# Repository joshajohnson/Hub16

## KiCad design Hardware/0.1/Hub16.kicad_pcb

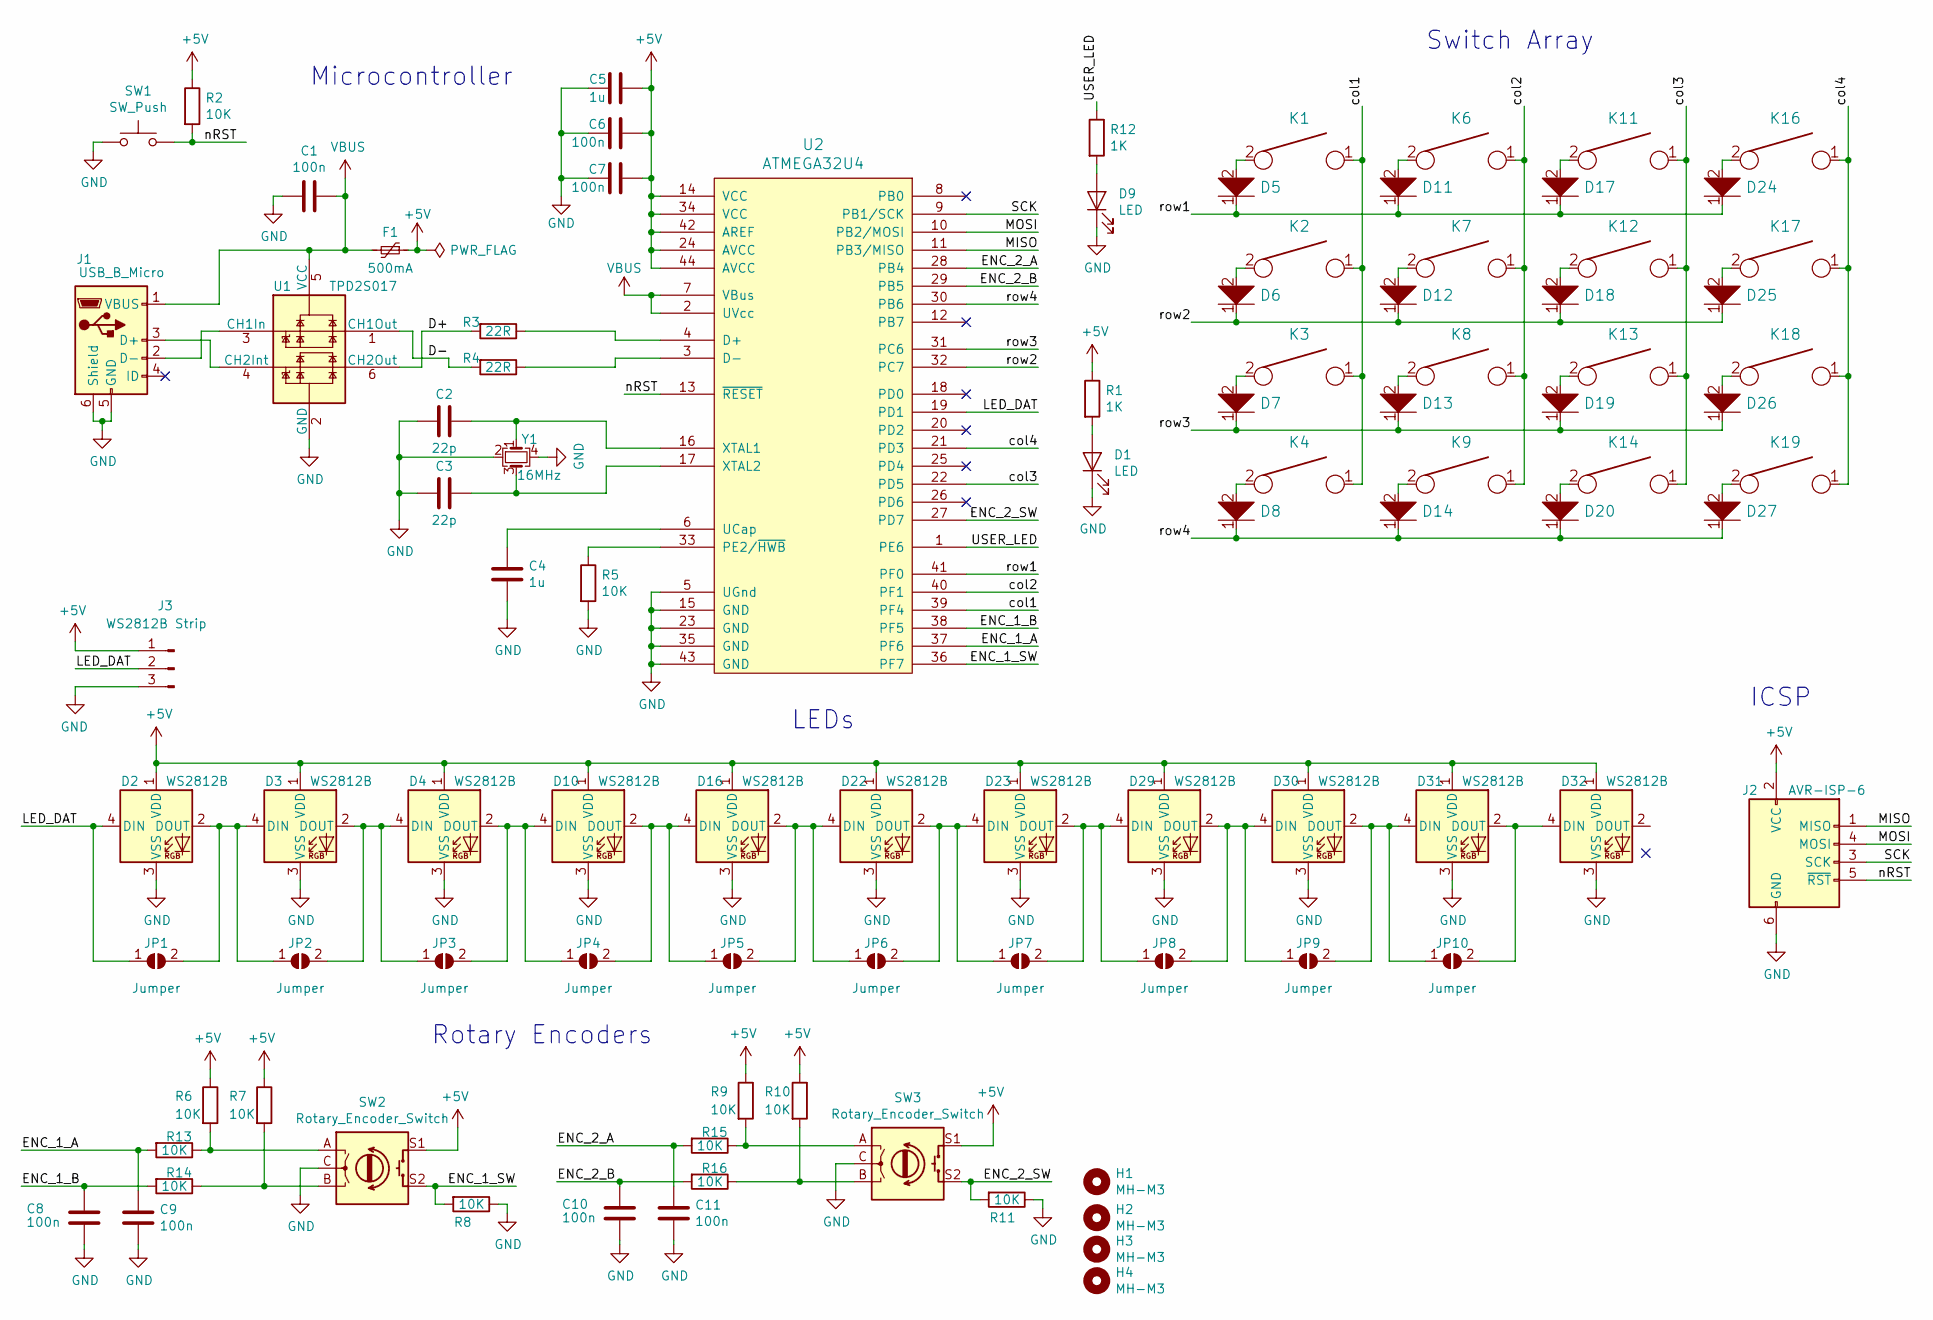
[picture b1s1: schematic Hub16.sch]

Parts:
C1, C6, C7, C8, C9, C10, C11: 100n; C_0603_1608Metric
C2, C3: 22p; C_0603_1608Metric
C4, C5: 1u; C_0603_1608Metric
D1, D9: LED; LED_0603_1608Metric
D2, D3, D4, D10, D16, D22, D23, D29, D30, D31, D32: WS2812B; LED_WS2812B_PLCC4_5.0x5.0mm_P3.2mm
D5, D6, D7, D8, D11, D12, D13, D14, D17, D18, D19, D20, D24, D25, D26, D27: D; D_SOD-323
F1: 500mA; Fuse_0805_2012Metric
H1, H2, H3, H4: MH-M3; MountingHole_3.2mm_M3_ISO14580
J1: USB_B_Micro; MicroUSB_Aliexpress
J2: AVR-ISP-6; AVR_Programmer_SMD
J3: WS2812B Strip; PinPad_1x03_P2.54mm
JP1, JP2, JP3, JP4, JP5, JP6, JP7, JP8, JP9, JP10: Jumper; SolderJumper-2_P1.3mm_Open_RoundedPad1.0x1.5mm
K1, K2, K3, K4, K6, K7, K8, K9, K11, K12, K13, K14, K16, K17, K18, K19: KEYSW; SW_Cherry_MX1A_1.00u_PCB
R1, R12: 1K; R_0603_1608Metric
R2, R5, R6, R7, R8, R9, R10, R11, R13, R14, R15, R16: 10K; R_0603_1608Metric
R3, R4: 22R; R_0603_1608Metric
SW1: SW_Push; Small_Tact_Switch
SW2, SW3: Rotary_Encoder_Switch; RotaryEncoder_Alps_EC11E-Switch_Vertical_H20mm_CircularMoun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
U1: TPD2S017; SOT-23-6
U2: ATMEGA32U4; TQFP-44_10x10mm_P0.8mm
Y1: 16MHz; Crystal_SMD_3225-4Pin_3.2x2.5mm

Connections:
+5V: C5.1, C6.2, C7.2, D2.1 (VDD), D3.1 (VDD), D4.1 (VDD), D10.1 (VDD), D16.1 (VDD), D22.1 (VDD), D23.1 (VDD), D29.1 (VDD), D30.1 (VDD), D31.1 (VDD), D32.1 (VDD), F1.1, J2.2 (VCC), J3.1, R1.1, R2.1, R6.1, R7.1, R9.1, R10.1, SW2.S1, SW3.S1, U2.14 (VCC), U2.24 (AVCC), U2.34 (VCC), U2.42 (AREF), U2.44 (AVCC)
/D+: R3.2, U1.6 (CH2Out)
/D-: R4.2, U1.1 (CH1Out)
/ENC_1_A: C9.1, R13.2, U2.37 (PF6)
/ENC_1_B: C8.1, R14.2, U2.38 (PF5)
/ENC_1_SW: R8.2, SW2.S2, U2.36 (PF7)
/ENC_2_A: C11.1, R15.2, U2.28 (PB4)
/ENC_2_B: C10.1, R16.2, U2.29 (PB5)
/ENC_2_SW: R11.2, SW3.S2, U2.27 (PD7)
/LED_DAT: D2.4 (DIN), J3.2, JP1.1 (A), U2.19 (PD1)
/MISO: J2.1 (MISO), U2.11 (PB3/MISO)
/MOSI: J2.4 (MOSI), U2.10 (PB2/MOSI)
/SCK: J2.3 (SCK), U2.9 (PB1/SCK)
/USER_LED: R12.1, U2.1 (PE6)
/col1: K1.1, K2.1, K3.1, K4.1, U2.39 (PF4)
/col2: K6.1, K7.1, K8.1, K9.1, U2.40 (PF1)
/col3: K11.1, K12.1, K13.1, K14.1, U2.22 (PD5)
/col4: K16.1, K17.1, K18.1, K19.1, U2.21 (PD3)
/nRST: J2.5 (~RST), R2.2, SW1.2, U2.13 (~RESET)
/row1: D5.1, D11.1, D17.1, D24.1, U2.41 (PF0)
/row2: D6.1, D12.1, D18.1, D25.1, U2.32 (PC7)
/row3: D7.1, D13.1, D19.1, D26.1, U2.31 (PC6)
/row4: D8.1, D14.1, D20.1, D27.1, U2.30 (PB6)
GND: C1.2, C2.2, C3.2, C4.2, C5.2, C6.1, C7.1, C8.2, C9.2, C10.2, C11.2, D1.1 (K), D2.3 (VSS), D3.3 (VSS), D4.3 (VSS), D9.1 (K), D10.3 (VSS), D16.3 (VSS), D22.3 (VSS), D23.3 (VSS), D29.3 (VSS), D30.3 (VSS), D31.3 (VSS), D32.3 (VSS), J1.5 (GND), J1.6 (Shield), J2.6 (GND), J3.3, R5.2, R8.1, R11.1, SW1.1, SW2.C, SW3.C, U1.2 (GND), U2.5 (UGnd), U2.15 (GND), U2.23 (GND), U2.35 (GND), U2.43 (GND), Y1.2, Y1.4
unnamed: C2.1, U2.16 (XTAL1), Y1.1
unnamed: C3.1, U2.17 (XTAL2), Y1.3
unnamed: C4.1, U2.6 (UCap)
unnamed: D1.2 (A), R1.2
unnamed: D2.2 (DOUT), D3.4 (DIN), JP1.2 (B), JP2.1 (A)
unnamed: D3.2 (DOUT), D4.4 (DIN), JP2.2 (B), JP3.1 (A)
unnamed: D5.2, K1.2
unnamed: D6.2, K2.2
unnamed: D7.2, K3.2
unnamed: D8.2, K4.2
unnamed: D9.2 (A), R12.2
unnamed: D10.2 (DOUT), D16.4 (DIN), JP4.2 (B), JP5.1 (A)
unnamed: D4.2 (DOUT), D10.4 (DIN), JP3.2 (B), JP4.1 (A)
unnamed: D11.2, K6.2
unnamed: D12.2, K7.2
unnamed: D13.2, K8.2
unnamed: D14.2, K9.2
unnamed: D16.2 (DOUT), D22.4 (DIN), JP5.2 (B), JP6.1 (A)
unnamed: D17.2, K11.2
unnamed: D18.2, K12.2
unnamed: D19.2, K13.2
unnamed: D20.2, K14.2
unnamed: D22.2 (DOUT), D23.4 (DIN), JP6.2 (B), JP7.1 (A)
unnamed: D23.2 (DOUT), D29.4 (DIN), JP7.2 (B), JP8.1 (A)
unnamed: D24.2, K16.2
unnamed: D25.2, K17.2
unnamed: D26.2, K18.2
unnamed: D27.2, K19.2
unnamed: D29.2 (DOUT), D30.4 (DIN), JP8.2 (B), JP9.1 (A)
unnamed: D30.2 (DOUT), D31.4 (DIN), JP9.2 (B), JP10.1 (A)
unnamed: D31.2 (DOUT), D32.4 (DIN), JP10.2 (B)
unnamed: J1.2 (D-), U1.3 (CH1In)
unnamed: J1.3 (D+), U1.4 (CH2Int)
unnamed: R3.1, U2.4 (D+)
unnamed: R4.1, U2.3 (D-)
unnamed: R5.1, U2.33 (PE2/~HWB)
unnamed: R10.2, R16.1, SW3.B
unnamed: R6.2, R13.1, SW2.A
unnamed: R7.2, R14.1, SW2.B
unnamed: R9.2, R15.1, SW3.A
VBUS: C1.1, F1.2, J1.1 (VBUS), U1.5 (VCC), U2.2 (UVcc), U2.7 (VBus)

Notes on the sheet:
Switch Array
LEDs
ICSP
Microcontroller
Rotary Encoders

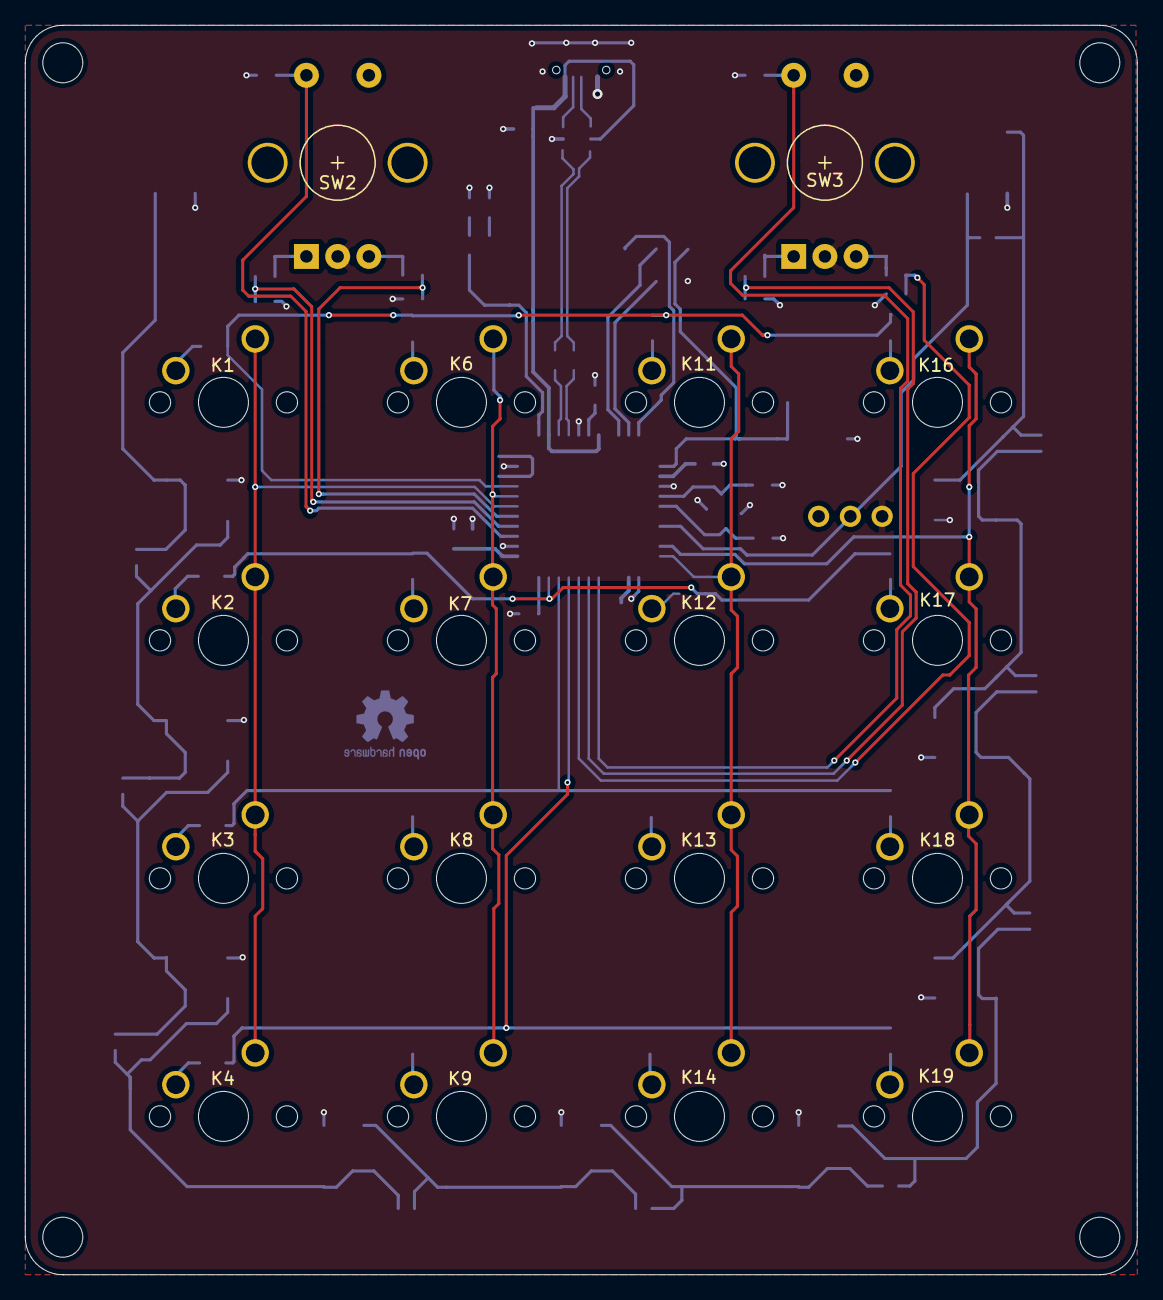
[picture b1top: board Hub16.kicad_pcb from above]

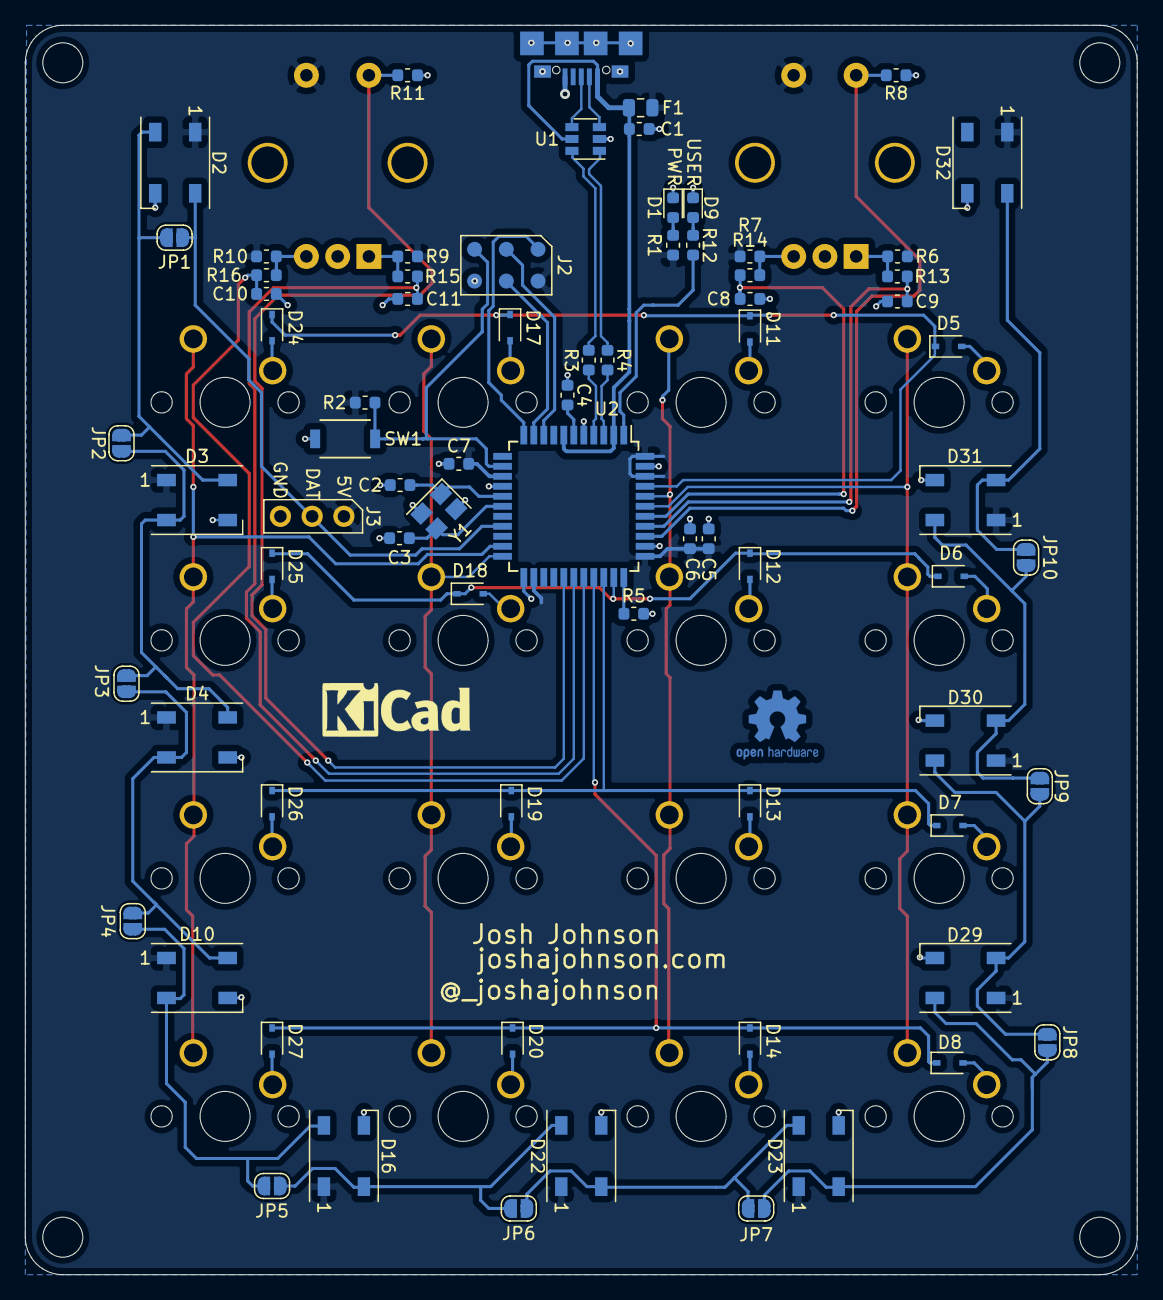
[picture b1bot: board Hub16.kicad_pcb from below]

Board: 2 copper layers, 89.0 x 100.0 mm, 96 parts (74 on the bottom side), 65 nets.
